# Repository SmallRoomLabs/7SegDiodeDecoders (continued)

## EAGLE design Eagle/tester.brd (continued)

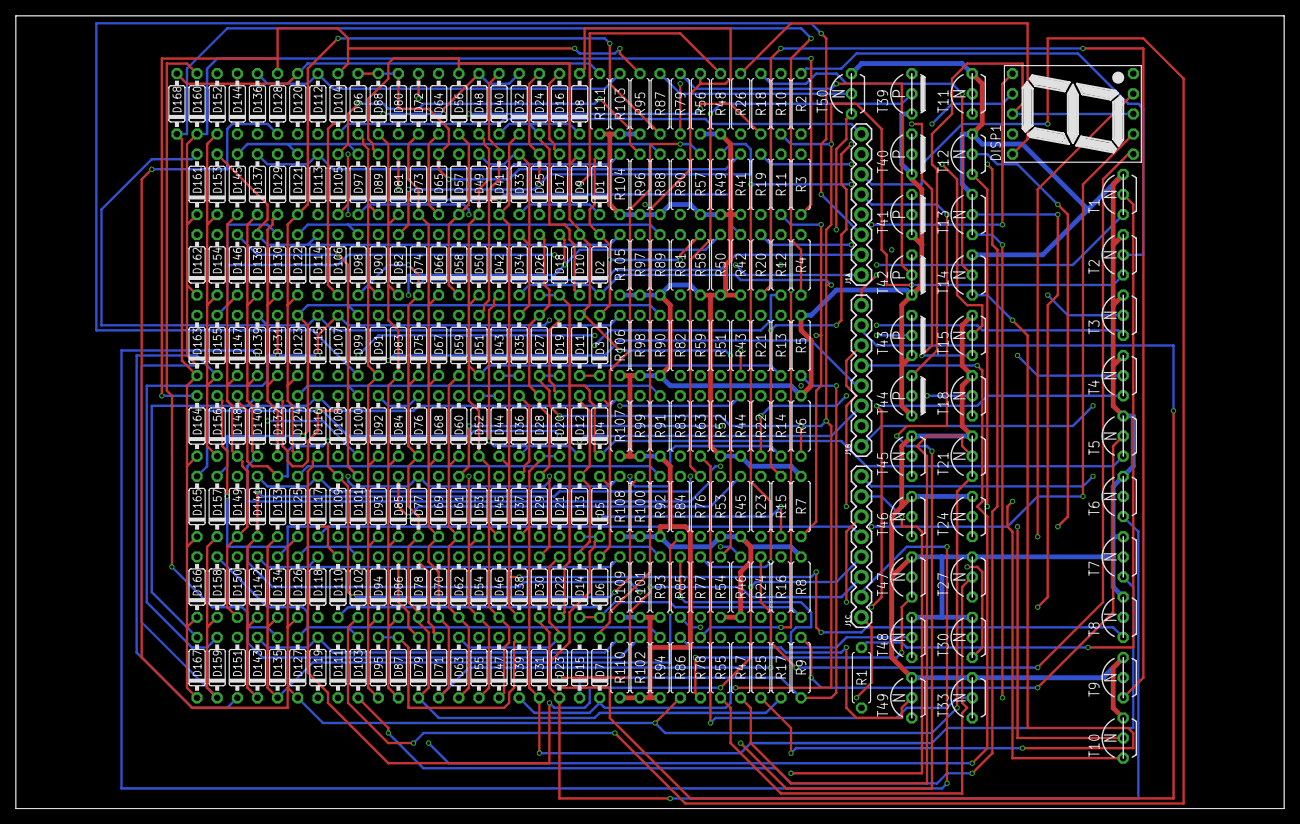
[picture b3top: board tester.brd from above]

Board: 4 copper layers, 160.0 x 100.0 mm, 287 parts (0 on the bottom side), 143 nets.

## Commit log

2020-11-01 Silk cleanup
